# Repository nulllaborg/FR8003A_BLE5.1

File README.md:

# FR8003A_BLE5.1
FR8003A BLE5.1 demo board

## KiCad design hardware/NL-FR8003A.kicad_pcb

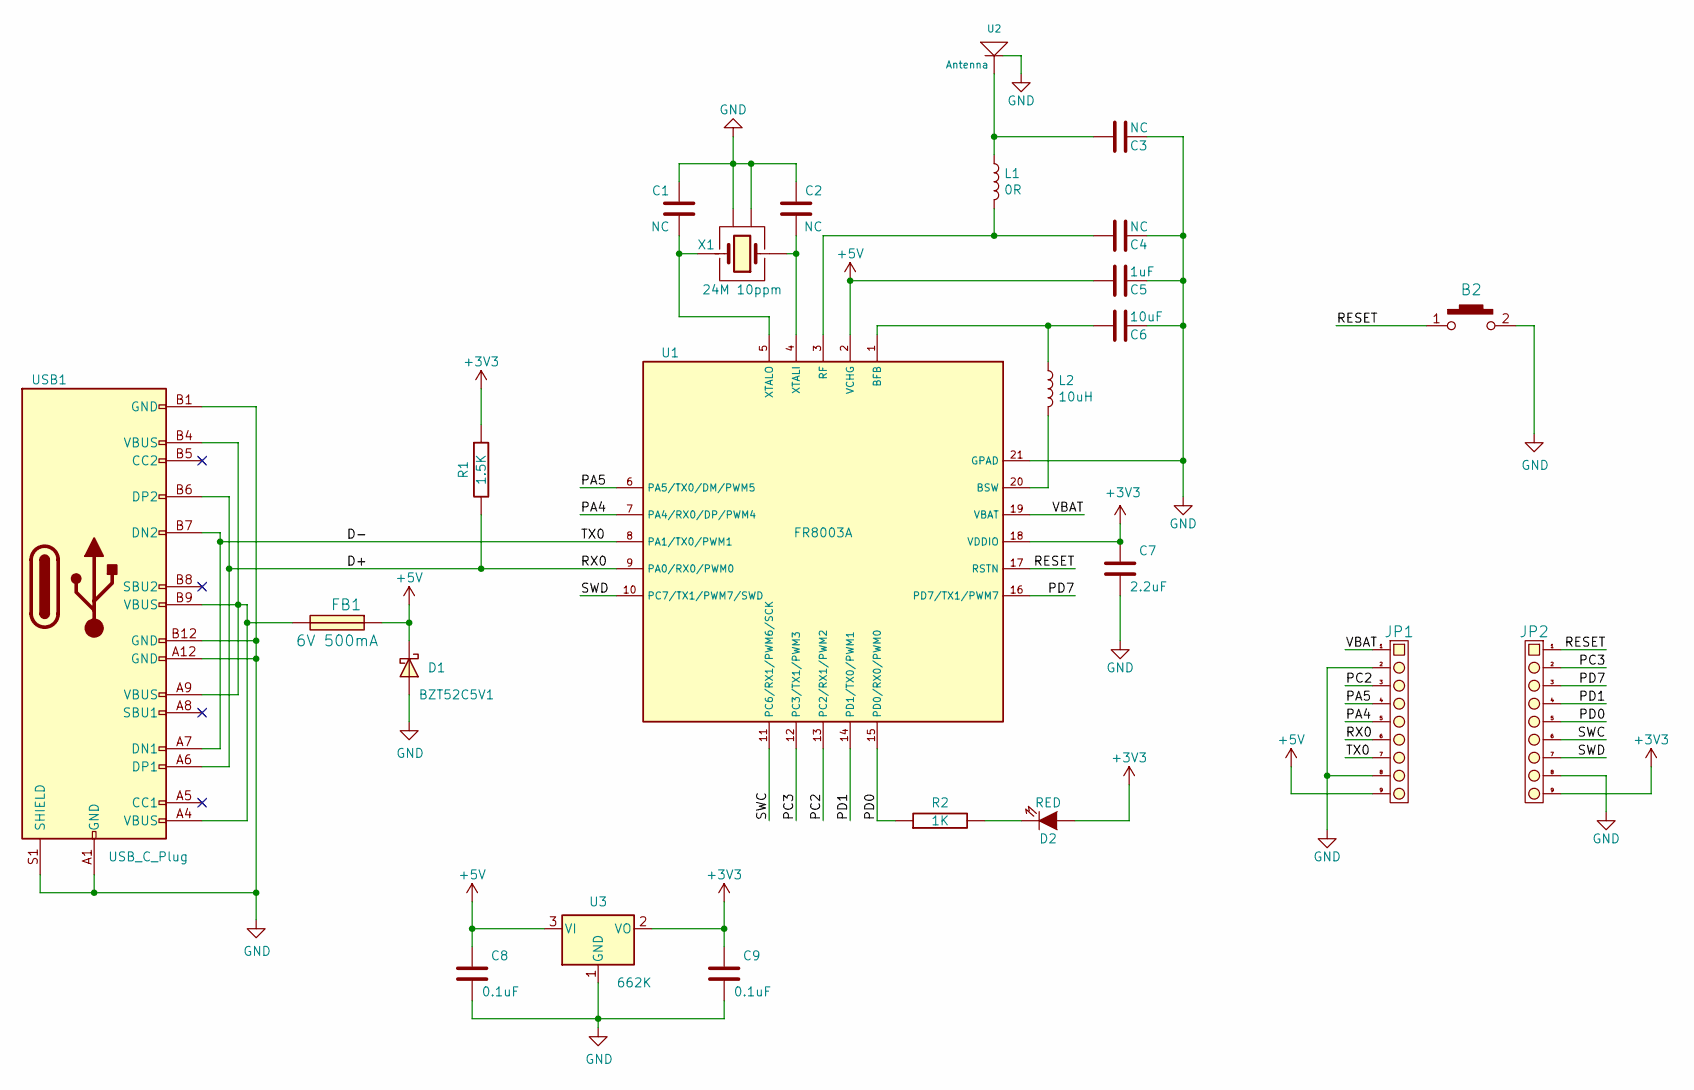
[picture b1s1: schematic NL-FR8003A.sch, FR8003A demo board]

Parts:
B2: Button_2; Panasonic_EVQPUJ_EVQPUA
C1, C2, C3, C4: NC; C_0603
C5: 1uF; C_0603
C6: 10uF; C_0603
C7: 2.2uF; C_0603
C8, C9: 0.1uF; C_0603
D1: BZT52C5V1; D_SOD-123
D2: RED; LED_0603
FB1: 6V 500mA; L_0805_2012Metric
JP1, JP2: JACK8; DIP-1.5Hole-2.54mm-Pitch-9P
L1: 0R; R_0603
L2: 10uH; L_0603
R1: 1.5K; R_0603
R2: 1K; R_0603
U1: FR8003A; QFN-20-1EP_3x3mm_P0.4mm_EP1.65x1.65mm
U2: Antenna; ANTENNA_IIFA_LEFT
U3: 662K; SOT-23
USB1: USB_C_Plug; USB_C_Receptacle_XKB_U262-16XN-4BVC11
X1: 24M 10ppm; Oscillator-SMD-4pin_3.2x2.5mm

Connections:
+3V3: C7.1, C9.1, D2.2 (+), JP2.9, R1.1, U1.18 (VDDIO), U3.2 (VO)
+5V: C5.2, C8.1, D1.1 (K), FB1.1, JP1.9, U1.2 (VCHG), U3.3 (VI)
/D+: JP1.6, R1.2, U1.9 (PA0/RX0/PWM0), USB1.A6 (DP1), USB1.B6 (DP2)
/D-: JP1.7, U1.8 (PA1/TX0/PWM1), USB1.A7 (DN1), USB1.B7 (DN2)
/PA4: JP1.5, U1.7 (PA4/RX0/DP/PWM4)
/PA5: JP1.4, U1.6 (PA5/TX0/DM/PWM5)
/PC2: JP1.3, U1.13 (PC2/RX1/PWM2)
/PC3: JP2.2, U1.12 (PC3/TX1/PWM3)
/PD0: JP2.5, R2.1, U1.15 (PD0/RX0/PWM0)
/PD1: JP2.4, U1.14 (PD1/TX0/PWM1)
/PD7: JP2.3, U1.16 (PD7/TX1/PWM7)
/RESET: B2.1, JP2.1, U1.17 (RSTN)
/SWC: JP2.6, U1.11 (PC6/RX1/PWM6/SCK)
/SWD: JP2.7, U1.10 (PC7/TX1/PWM7/SWD)
/VBAT: JP1.1, U1.19 (VBAT)
GND: B2.2, C1.2, C2.2, C3.1, C4.1, C5.1, C6.1, C7.2, C8.2, C9.2, D1.2 (A), JP1.2, JP1.8, JP2.8, U1.21 (GPAD), U2.2, U3.1 (GND), USB1.A1 (GND), USB1.A12 (GND), USB1.B1 (GND), USB1.B12 (GND), USB1.S1 (SHIELD), X1.2, X1.4
unnamed: C1.1, U1.5 (XTALO), X1.3
unnamed: C2.1, U1.4 (XTALI), X1.1
unnamed: C3.2, L1.1, U2.1
unnamed: C4.2, L1.2, U1.3 (RF)
unnamed: C6.2, L2.1, U1.1 (BFB)
unnamed: D2.1 (-), R2.2
unnamed: FB1.2, USB1.A4 (VBUS), USB1.A9 (VBUS), USB1.B4 (VBUS), USB1.B9 (VBUS)
unnamed: L2.2, U1.20 (BSW)

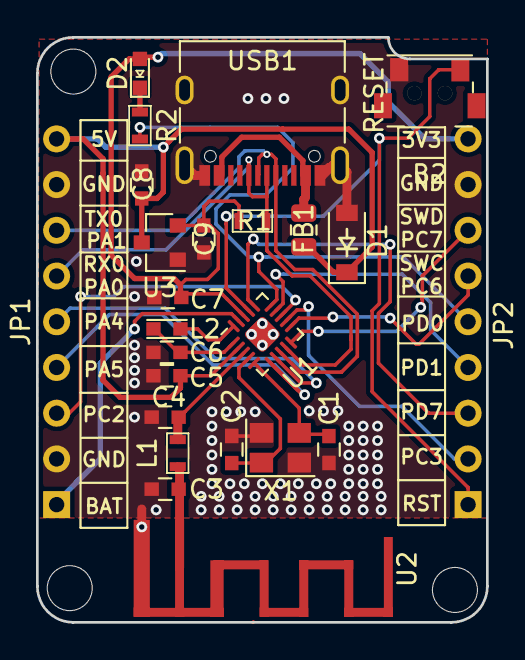
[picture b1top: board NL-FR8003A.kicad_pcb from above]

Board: 2 copper layers, 25.0 x 32.5 mm, 24 parts (0 on the bottom side), 24 nets.

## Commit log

2021-12-01 add demo board hw
2021-12-15 add sch lib
2022-01-04 update lib
2022-03-26 update module
